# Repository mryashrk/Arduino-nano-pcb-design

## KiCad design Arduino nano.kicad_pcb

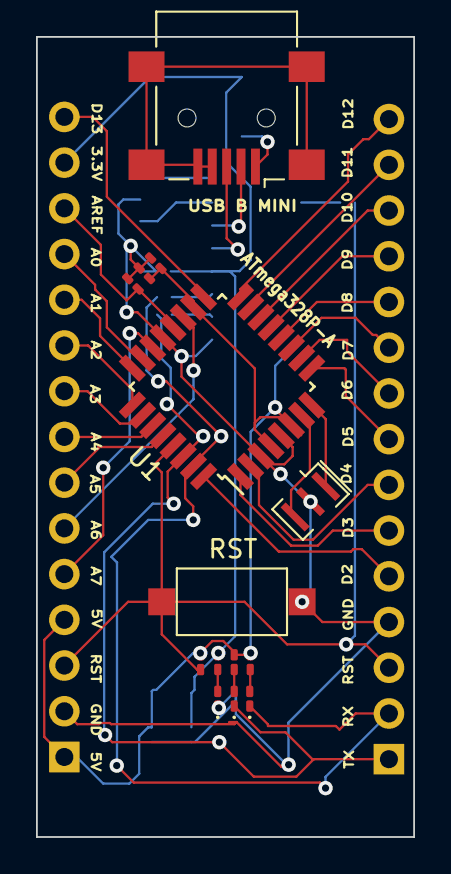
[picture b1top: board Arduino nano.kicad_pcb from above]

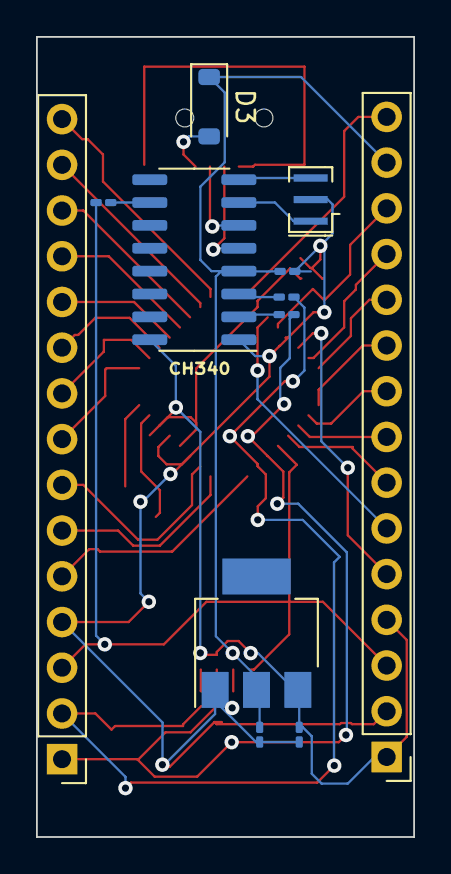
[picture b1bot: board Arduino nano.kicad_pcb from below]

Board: 2 copper layers, 21.0 x 44.5 mm, 26 parts (12 on the bottom side), 41 nets.

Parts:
C1, C3, C6, C8: 100nf; C_0201_0603Metric_Pad0.64x0.40mm_HandSolder
C4, C5: 22u; C_0201_0603Metric_Pad0.64x0.40mm_HandSolder
C7: 4.7uf; C_0201_0603Metric_Pad0.64x0.40mm_HandSolder
D2, D4, D5: LED; LED_0201_0603Metric_Pad0.64x0.40mm_HandSolder
D3: MBR0520LT; D_SOD-123
J1: USB_B_Mini; USB_Mini-B_Lumberg_2486_01_Horizontal
J2, J3: Conn_01x15_Pin; PinHeader_1x15_P2.54mm_Vertical
R2, R3, R4, R5, R6: 1K; R_0201_0603Metric_Pad0.64x0.40mm_HandSolder
R7: 10k; R_0201_0603Metric_Pad0.64x0.40mm_HandSolder
SW1: RST; SW_SPST_CK_RS282G05A3
U1: ATmega328P-A; TQFP-32_7x7mm_P0.8mm
U2: CH340G; SOIC-16_3.9x9.9mm_P1.27mm
U4: TLV1117LV-3.3; SOT-223
Y3, Y4: Crystal_GND2; Resonator_SMD_Murata_CSTxExxV-3Pin_3.0x1.1mm

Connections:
+3.3V: C1.2, C5.1, D3.1 (K), J3.14, R4.2, U2.4 (V3), U4.2 (VO)
+5V: C4.1, C6.1, C7.1, J3.1, J3.4, R5.2, R6.2, R7.1, U1.4 (VCC), U1.6 (VCC), U1.18 (AVCC), U2.16 (VCC), U4.3 (VI)
/A0: J3.12, U1.23 (PC0)
/A1: J3.11, U1.24 (PC1)
/A2: J3.10, U1.25 (PC2)
/A3: J3.9, U1.26 (PC3)
/A4: J3.8, U1.27 (PC4)
/A5: J3.7, U1.28 (PC5)
/A6: J3.6, U1.19 (ADC6)
/A7: J3.5, U1.22 (ADC7)
/AREF: C8.2, J3.13, U1.20 (AREF)
/D2: J2.5, U1.32 (PD2)
/D3: J2.6, U1.1 (PD3)
/D4: J2.7, U1.2 (PD4)
/D5: J2.8, U1.9 (PD5)
/D6: J2.9, U1.10 (PD6)
/D7: J2.10, U1.11 (PD7)
/D8: J2.11, U1.12 (PB0)
/D9: J2.12, U1.13 (PB1)
/D10: J2.13, U1.14 (PB2)
/D11: J2.14, U1.15 (PB3)
/D12: J2.15, U1.16 (PB4)
/D13: J3.15, U1.17 (PB5)
/RST: C3.2, J2.3, J3.3, R7.2, SW1.3 (K), U1.29 (~RESET/PC6)
/RX: D5.1 (K), J2.2, R3.1, U1.31 (PD1)
/TX: D4.1 (K), J2.1, R2.2, U1.30 (PD0)
GND: C1.1, C4.2, C5.2, C6.2, C7.2, C8.1, D2.1 (K), J2.4, J3.2, SW1.1, U1.3 (GND), U1.5 (GND), U1.21 (GND), U2.1 (GND), U4.1 (GND), Y3.2, Y4.2
unnamed: D2.2 (A), R4.1
unnamed: D3.2 (A), J1.1 (VBUS)
unnamed: D4.2 (A), R5.1
unnamed: D5.2 (A), R6.1
unnamed: J1.3 (D+), U2.5 (UD+)
unnamed: J1.2 (D-), U2.6 (UD-)
unnamed: J1.4 (ID), J1.5 (GND), J1.6 (Shield)
unnamed: U1.7 (XTAL1/PB6), Y3.3
unnamed: U1.8 (XTAL2/PB7), Y3.1
unnamed: R3.2, U2.3 (RXD)
unnamed: R2.1, U2.2 (TXD)
unnamed: U2.7 (XI), Y4.1
unnamed: U2.8 (XO), Y4.3
unnamed: C3.1, U2.10 (~DSR)
